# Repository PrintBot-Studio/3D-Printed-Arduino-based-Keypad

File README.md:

# Project 1: F16 Viper Throttle and Keypad

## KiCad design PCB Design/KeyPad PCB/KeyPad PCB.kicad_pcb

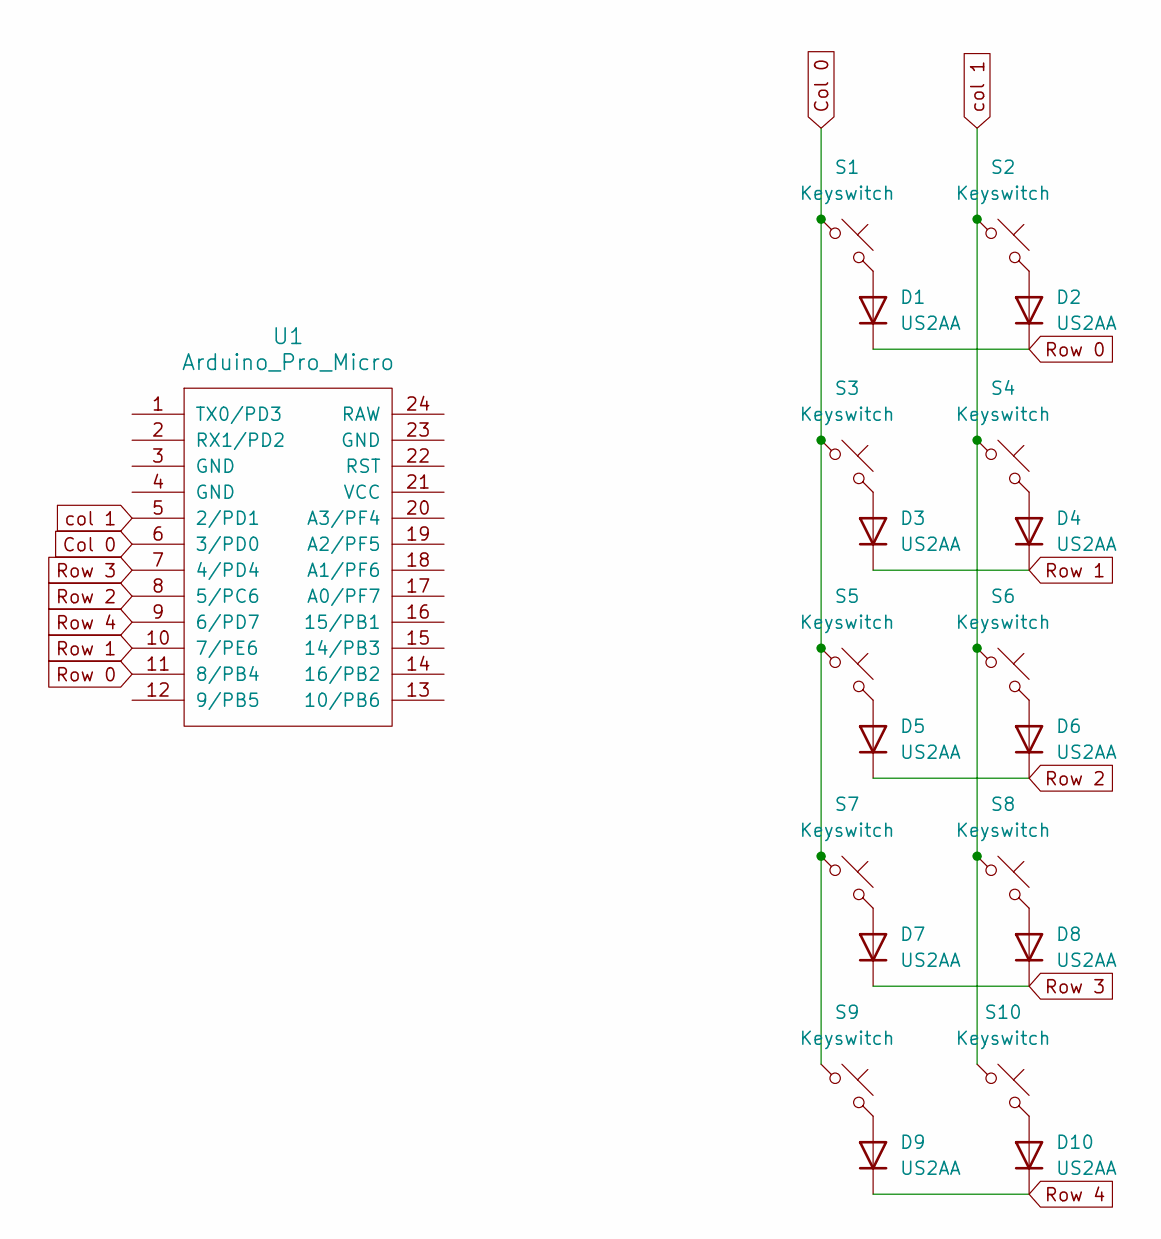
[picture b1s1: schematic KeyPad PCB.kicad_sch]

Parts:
D1, D2, D3, D4, D5, D6, D7, D8, D9, D10: US2AA; Resistor_0805
S1, S2, S3, S4, S5, S6, S7, S8, S9, S10: Keyswitch; MX_PCB_1.00u
U1: Arduino_Pro_Micro

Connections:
Col 0: S1.1, S3.1, S5.1, S7.1, S9.1, U1.6 (3/PD0)
unnamed: D1.2 (A), S1.2
unnamed: D2.2 (A), S2.2
unnamed: D3.2 (A), S3.2
unnamed: D4.2 (A), S4.2
unnamed: D5.2 (A), S5.2
unnamed: D6.2 (A), S6.2
unnamed: D7.2 (A), S7.2
unnamed: D8.2 (A), S8.2
unnamed: D9.2 (A), S9.2
unnamed: D10.2 (A), S10.2
Row 0: D1.1 (K), D2.1 (K), U1.11 (8/PB4)
Row 1: D3.1 (K), D4.1 (K), U1.10 (7/PE6)
Row 2: D5.1 (K), D6.1 (K), U1.8 (5/PC6)
Row 3: D7.1 (K), D8.1 (K), U1.7 (4/PD4)
Row 4: D9.1 (K), D10.1 (K), U1.9 (6/PD7)
col 1: S2.1, S4.1, S6.1, S8.1, S10.1, U1.5 (2/PD1)

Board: 2 copper layers, 21 parts (0 on the bottom side), 17 nets, no tracks yet.

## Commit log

2024-12-03 3D Printed Adrunio Based Keypad
2024-12-03 adding code for arduino
2024-12-04 adding new code for uno
2024-12-04 Keypad & Throttle Layout.Added Flat KeyCaps , Relocated Toggle Swicth & Potentiometer Position.
2024-12-04 Various changes has been made.Swicth's and Potentiometer position's has been updated.Component's Bracket Below FacePlate as heen Added.
2024-12-04 Specific Keyboard Key Layout
2024-12-06 adding function to arduino keypad
2024-12-07 adding HID to the arduino KeyPads
2024-12-07 adding arduino joystick as a shortcut
2024-12-07 Reconfigured the Dimentions's of the Keypad.Added 2 Additional Swicth Key's.Currently Working on Rotational Potentiometer Support for Throttle instade of Slide Pot.
2024-12-08 Almost Everything is Done . Readjusted Throttle Stand length . Completated the Throttle Base Support
2024-12-08 Implemented Hand Rest to the Base and Added Base Support . Fixed the Directional Keycaps flickaring.
2024-12-08 Readjusted the Base Length
2024-12-08 Adden Vibretion's Motor Base to Keypad
2024-12-08 Controller's Side View IMG
2024-12-08 Relocated Old Version
2024-12-08 Added proper housing & Support for Vibretion Motor And Added Support to lower End of the shaft
2024-12-09 Expened Base & Faceplate Length . Add Knob for potensiometer Also Made shaft Thinner
2024-12-09 Readjusted Knob Size , Added Second Five-Ways Tactile Swicth at the front on thr Throttle
2024-12-09 Updated Keybaord Layout Binding For Adriuno Programming. 10 Mecha Switch , 5 Directional Switch , 2 Modifier's , 2 5-Way Tactile Swicth
2024-12-15 Added Bearing Support for Potentiometer rotation and Updated the shaft to support bearing housing.updated the faceplate hole according to Bearing Shaft.Updated potentiometer Support to Base
2024-12-15 Reloacted the Throttle shaft to Old File's Folder
2024-12-15 updated Base and Face plate alienment
2024-12-15 Directional Key's Updated
2024-12-15 Added Reference Model of Five Dic Btn - Updated % way Washer Inner size
2024-12-15 Updated throttle Side panel & Grip with Five way BTN Housing
2024-12-15 ADDED PROPER SCREW HOLE TO BEARING SUPPORT , BASE AND THROTTLE BEARING SHAFT
2024-12-18 Updated Faceplate with new Disgn , Updated Base to Supporting Rotating Throttle by Gear Mechanism , Reduced Knop Size , added After Burner Lever , Added Gear Levers , Added Gear to rotate the potenti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
2024-12-18 Version 3.0 Structure and Layout ( Key binding Layout not Complte ) Imgage is provided .
2024-12-19 Updated Base and Faceplate with proper M3 Screw hole's..
2024-12-19 affed imgage of Throttle BTN Position
2024-12-20 Adjusted Directional keys and keycap's
2024-12-28 update: macropad code updated
2025-01-03 Deleted file
    inside Knob,Hat ,Swicth folder
2025-01-03 Added Anti Elev Knob , Directional Keys , Directional Switch BTN , Faceplate Knob 2,Faceplate Knob,Faceplate Side Pot Lever,Joystick knob 1,Keypad KeysKeypad Keys,Speed Break Slide Btn,Throttle Dogfi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
2025-01-03 Deleting Previous throttle version model's . After Burner Lever,front side,Gear 2x,Gear Lever 1,Gear Lever 2,Lower Side,Throttle Holder,upper side
2025-01-03 Final Updated Version's of Afterburner Lever,Gear 1,Gear 2,Throtte Joystick Cover,Throttle Bottom Side ,Throttle Front Side,Throttle Holder,Throttle Lever 1,Throttle Lever 2,Throttle Top Side
2025-01-03 deleting previous version's of Directional KeyCaps,Directional Keys,FacePlate,Pot Knob
2025-01-03 Final Updated Version of Base , Base PCB Bracket , Directional Switch PCB Bracket , Faceplate , Mechanical Switch PCB Bracket
2025-01-03 Lockheed Martin Custom F16 Throttle Quadrent 3D Model is now Fully complete and Ready to print.Added image's of Final Version Model 2,Final Version Model Internal View,Final Version Model Top View,Fi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
